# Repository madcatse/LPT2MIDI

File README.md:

# LPT2MIDI
- LPT2MIDI is a parallel printer port (LPT) to MIDI adapter.
- KiCAD 10 PCB project is included.
- Uses Arduino IRQ to trigger pin reads and forwards the data to MIDI serial buffer (MIDI uses 31250 bps).
- A simple port trapping code for MS-DOS is included. This for the time being works for direct midi commands to port 330h only.
- Quickly modified version of SOFTMPU for MPU-401 compatibility.
- Tested with mt32pi and Secret if Monkey Island.
- Requires power through USB on Arduino Nano while operating.

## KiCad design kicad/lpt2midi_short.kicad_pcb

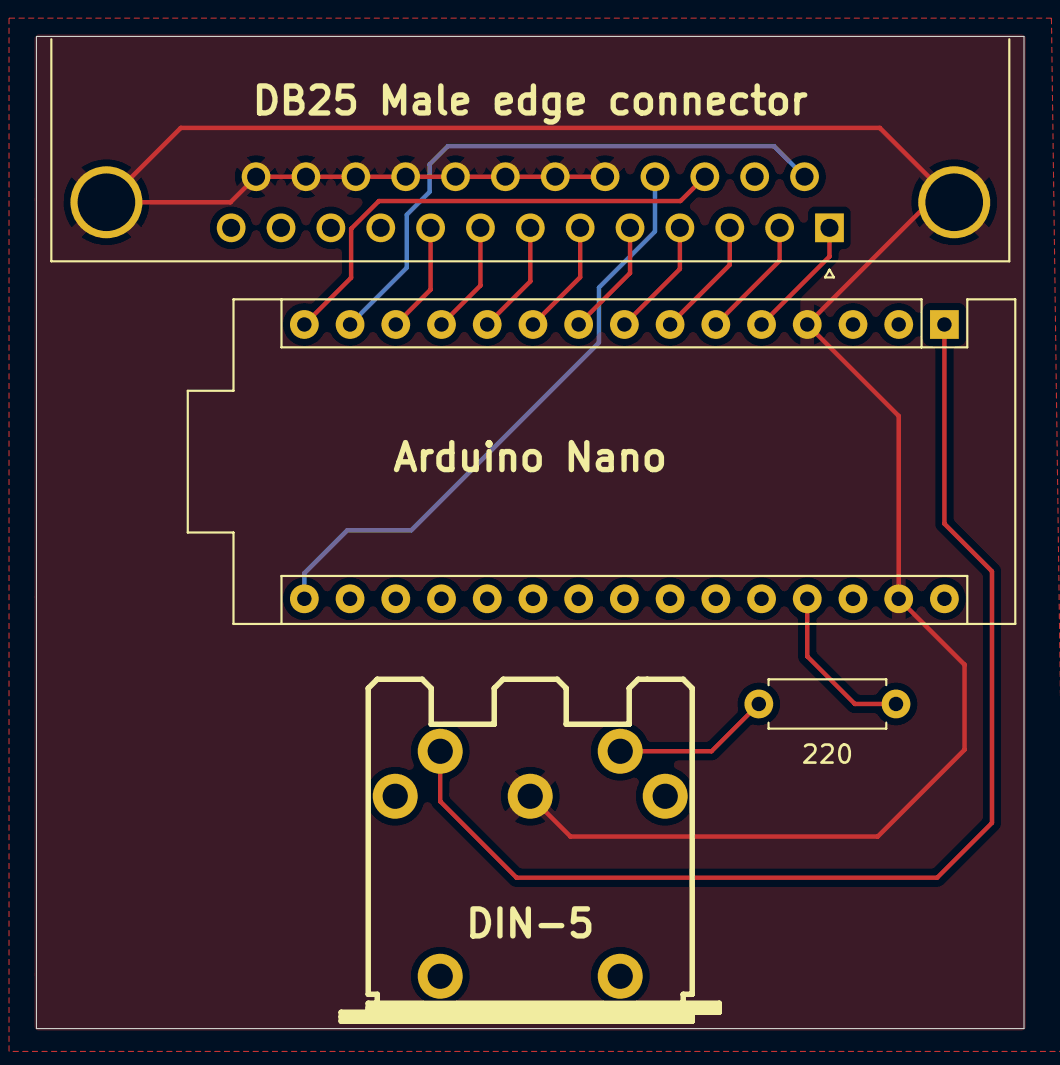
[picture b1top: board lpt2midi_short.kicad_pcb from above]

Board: 2 copper layers, 54.9 x 55.1 mm, 4 parts (0 on the bottom side), 16 nets.

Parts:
220: 220; R_Axial_DIN0207_L6.3mm_D2.5mm_P7.62mm_Horizontal
J1: DIN-5; din-5
J2: DB25_Male_MountingHoles; DSUB-25_Male_Horizontal_P2.77x2.84mm_EdgePinOffset7.70mm_Ho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
U1: Arduino_Nano

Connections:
/SELECTPRN: J2.17, U1.16 (D13)
/STROBE: J2.1, U1.5 (D2)
GND: J1.2, J2.0 (PAD), J2.18, J2.19, J2.20, J2.21, J2.22, J2.23, J2.24, J2.25, U1.4 (GND), U1.29 (GND)
unnamed: 220.1, J1.4
unnamed: J1.5, U1.1 (D1/TX)
unnamed: J2.2, U1.6 (~D3)
unnamed: J2.3, U1.7 (D4)
unnamed: J2.4, U1.8 (~D5)
unnamed: J2.5, U1.9 (~D6)
unnamed: J2.6, U1.10 (D7)
unnamed: J2.7, U1.11 (D8)
unnamed: J2.8, U1.12 (~D9)
unnamed: J2.9, U1.13 (~D10)
unnamed: J2.14, U1.14 (~D11)
unnamed: J2.16, U1.15 (D12)
unnamed: 220.2, U1.27 (+5V)

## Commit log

2026-06-09 Initial full project upload
